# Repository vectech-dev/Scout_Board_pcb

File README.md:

# Pinout for Scout Board

## Motor Control

* In1 - GPIO_21/J3_18
* In2 - GPIO_35/J3_13

## Motor Switches

* Sw1 - GPIO_15/J1_8
* Sw2 - GPIO_6/J1_6

## Buttons 

* Flip Button - GPIO_7/J1_7
* Capture Button - GPIO_18/J1_11

## SBC

* Power - GPIO_8/J1_12

## Lights

* TopLights - Gpio_13/J1_19
* BottomLights - Gpio_14/J1_20

## Communication 

* RxD(ESP) - Gpio_16/J1_9
* TxD(ESP) - Gpio_17/J1_10

## Extra Provosions

* Button3 - Gpio_9
* Button4 - Gpio_10
* Button5 - Gpio_11
* Button6 - Gpio_12

* Conn1 - Gpio_2
* Conn2 - Gpio_3
* Conn3 - Gpio_4
* Conn4 - Gpio_5

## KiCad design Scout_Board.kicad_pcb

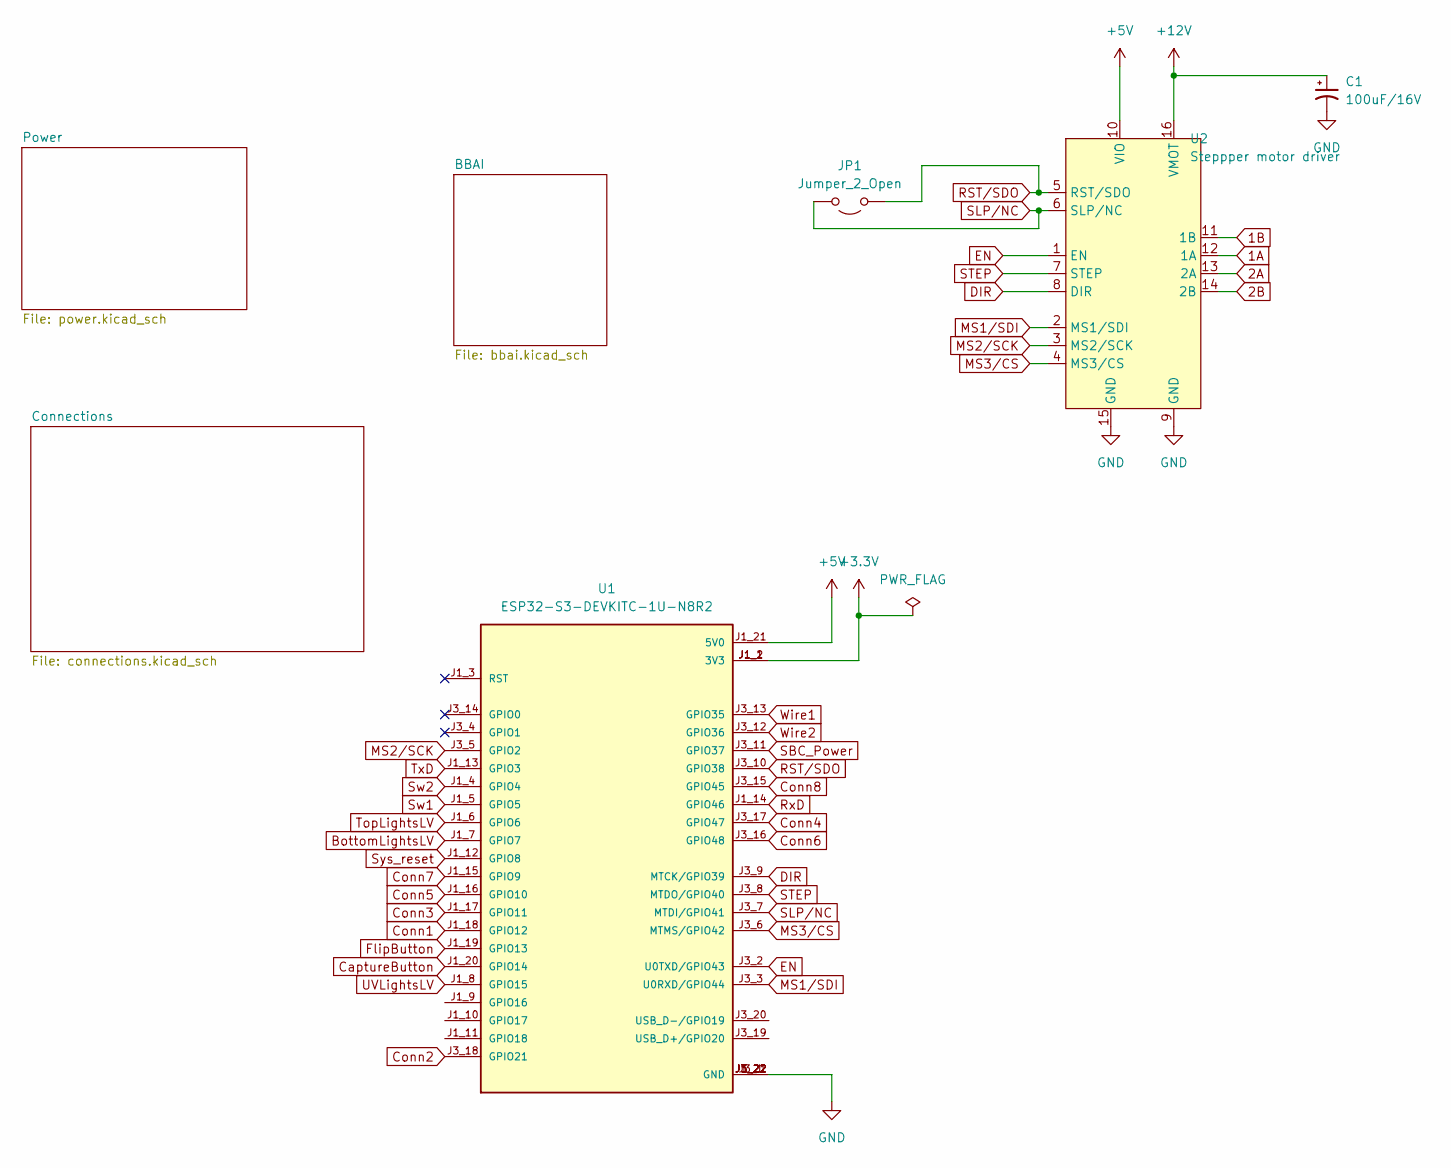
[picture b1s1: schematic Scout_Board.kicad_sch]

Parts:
C1: 100uF/16V; CP_Elec_6.3x5.9; Part Number 865080343009; LCSC C111600
JP1: Jumper_2_Open; TestPoint_2Pads_Pitch2.54mm_Drill0.8mm; LCSC C920781
U1: ESP32-S3-DEVKITC-1U-N8R2; XCVR_ESP32-S3-DEVKITC-1-N8R2; PARTREV 5.3
U2: Steppper motor driver; Pololu_Breakout-16_15.2x20.3mm

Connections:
1A: U2.12 (1A); also elsewhere on the board
1B: U2.11 (1B); also elsewhere on the board
2A: U2.13 (2A); also elsewhere on the board
2B: U2.14 (2B); also elsewhere on the board
5V: U1.J1_21 (5V0), U2.10 (VIO); also elsewhere on the board
+3.3V: U1.J1_1 (3V3), U1.J1_2 (3V3); also elsewhere on the board
+12V: C1.1, U2.16 (VMOT); also elsewhere on the board
BottomLightsLV: U1.J1_7 (GPIO7); also elsewhere on the board
CaptureButton: U1.J1_20 (GPIO14); also elsewhere on the board
Conn1: U1.J1_18 (GPIO12); also elsewhere on the board
Conn2: U1.J3_18 (GPIO21); also elsewhere on the board
Conn3: U1.J1_17 (GPIO11); also elsewhere on the board
Conn4: U1.J3_17 (GPIO47); also elsewhere on the board
Conn5: U1.J1_16 (GPIO10); also elsewhere on the board
Conn6: U1.J3_16 (GPIO48); also elsewhere on the board
Conn7: U1.J1_15 (GPIO9); also elsewhere on the board
Conn8: U1.J3_15 (GPIO45); also elsewhere on the board
DIR: U1.J3_9 (MTCK/GPIO39), U2.8 (DIR)
EN: U1.J3_2 (U0TXD/GPIO43), U2.1 (EN)
FlipButton: U1.J1_19 (GPIO13); also elsewhere on the board
GND: C1.2, U1.J1_22 (GND), U1.J3_1 (GND), U1.J3_21 (GND), U1.J3_22 (GND), U2.9 (GND), U2.15 (GND); also elsewhere on the board
MS1/SDI: U1.J3_3 (U0RXD/GPIO44), U2.2 (MS1/SDI)
MS2/SCK: U1.J3_5 (GPIO2), U2.3 (MS2/SCK)
MS3/CS: U1.J3_6 (MTMS/GPIO42), U2.4 (MS3/CS)
RST/SDO: JP1.1 (A), U1.J3_10 (GPIO38), U2.5 (RST/SDO)
RxD: U1.J1_14 (GPIO46); also elsewhere on the board
SBC_Power: U1.J3_11 (GPIO37); also elsewhere on the board
SLP/NC: JP1.2 (B), U1.J3_7 (MTDI/GPIO41), U2.6 (SLP/NC)
STEP: U1.J3_8 (MTDO/GPIO40), U2.7 (STEP)
Sw1: U1.J1_5 (GPIO5); also elsewhere on the board
Sw2: U1.J1_4 (GPIO4); also elsewhere on the board
Sys_reset: U1.J1_12 (GPIO8); also elsewhere on the board
TopLightsLV: U1.J1_6 (GPIO6); also elsewhere on the board
TxD: U1.J1_13 (GPIO3); also elsewhere on the board
UVLightsLV: U1.J1_8 (GPIO15); also elsewhere on the board
Wire1: U1.J3_13 (GPIO35); also elsewhere on the board
Wire2: U1.J3_12 (GPIO36); also elsewhere on the board

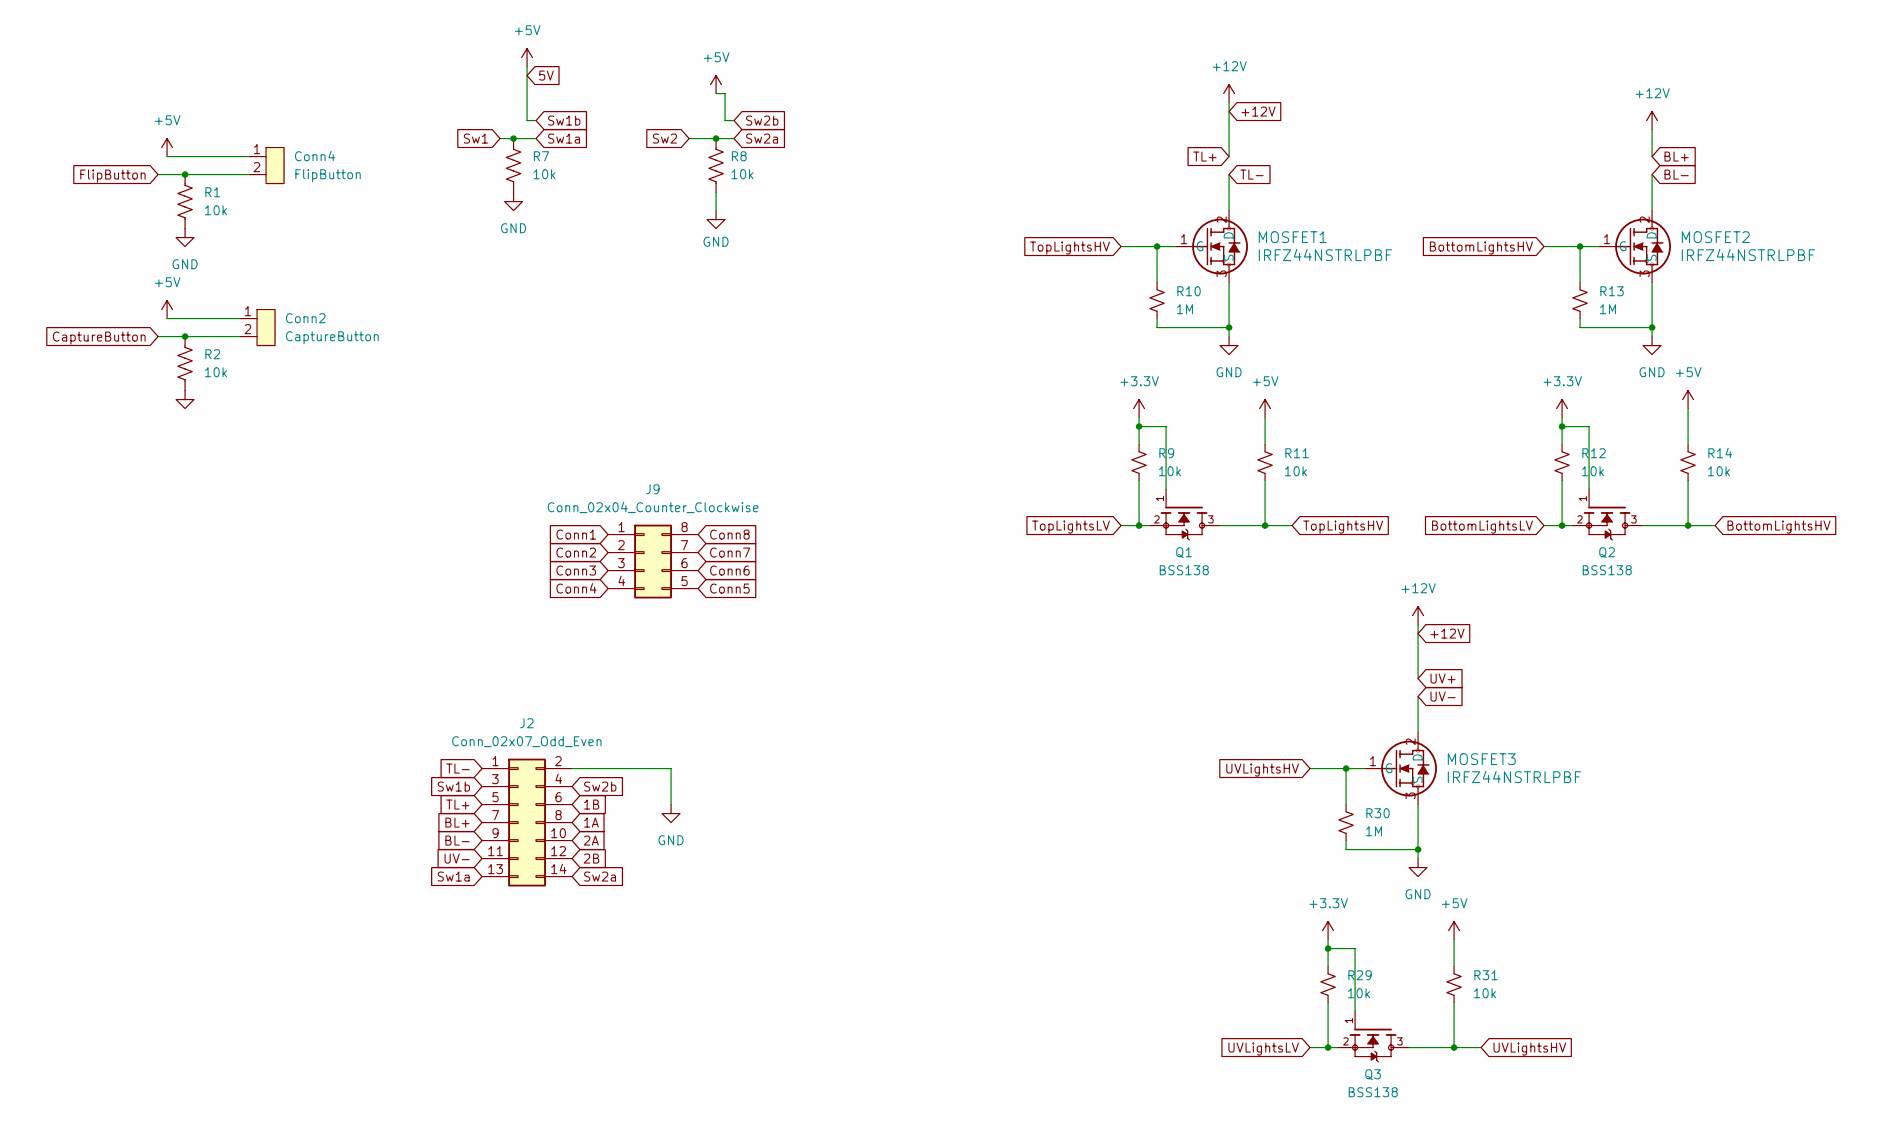
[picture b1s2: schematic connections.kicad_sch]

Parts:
Conn2: CaptureButton; JST_XH_B2B-XH-AM_1x02_P2.50mm_Vertical; Part Number B2B-XH-A-M; LCSC C158012
Conn4: FlipButton; JST_XH_B2B-XH-AM_1x02_P2.50mm_Vertical; Part Number B2B-XH-A-M; LCSC C158012
J2: Conn_02x07_Odd_Even; IDC-Header_2x07_P2.54mm_Vertical; Part Number 3020-14-0100-00; LCSC C17661375
J9: Conn_02x04_Counter_Clockwise; PinSocket_2x04_P2.54mm_Vertical
MOSFET1, MOSFET2, MOSFET3: IRFZ44NSTRLPBF; DPAK254P1524X483-3N; Part Number IRFZ44NSTRLPBF; LCSC C58228
Q1, Q2, Q3: BSS138; SOT-323_DIO; PARTREV 30 Jan 2018; LCSC C5250986
R1, R2, R7, R8, R9, R11, R12, R14, R29, R31: 10k; R_0603_1608Metric_Pad0.98x0.95mm_HandSolder; Part Number RMCF0603JT10K0; LCSC C98220
R10, R13, R30: 1M; R_0603_1608Metric_Pad0.98x0.95mm_HandSolder; Part Number ERJ-3EKF1004V; LCSC C4060339

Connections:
1A: J2.8; also elsewhere on the board
1B: J2.6; also elsewhere on the board
2A: J2.10; also elsewhere on the board
2B: J2.12; also elsewhere on the board
5V: Conn2.1, Conn4.1, J2.3, J2.4, R11.1, R14.1, R31.1; also elsewhere on the board
+3.3V: Q1.1, Q2.1, Q3.1, R9.1, R12.1, R29.1; also elsewhere on the board
+12V: J2.5, J2.7; also elsewhere on the board
BL-: J2.9, MOSFET2.2 (D)
BottomLightsHV: MOSFET2.1 (G), Q2.3, R13.1, R14.2
BottomLightsLV: Q2.2, R12.2; also elsewhere on the board
CaptureButton: Conn2.2, R2.1; also elsewhere on the board
Conn1: J9.1; also elsewhere on the board
Conn2: J9.2; also elsewhere on the board
Conn3: J9.3; also elsewhere on the board
Conn4: J9.4; also elsewhere on the board
Conn5: J9.5; also elsewhere on the board
Conn6: J9.6; also elsewhere on the board
Conn7: J9.7; also elsewhere on the board
Conn8: J9.8; also elsewhere on the board
FlipButton: Conn4.2, R1.1; also elsewhere on the board
GND: J2.2, MOSFET1.3 (S), MOSFET2.3 (S), MOSFET3.3 (S), R1.2, R2.2, R7.2, R8.2, R10.2, R13.2, R30.2; also elsewhere on the board
Sw1: J2.13, R7.1; also elsewhere on the board
Sw2: J2.14, R8.1; also elsewhere on the board
TL-: J2.1, MOSFET1.2 (D)
TopLightsHV: MOSFET1.1 (G), Q1.3, R10.1, R11.2
TopLightsLV: Q1.2, R9.2; also elsewhere on the board
UV-: J2.11, MOSFET3.2 (D)
UVLightsHV: MOSFET3.1 (G), Q3.3, R30.1, R31.2
UVLightsLV: Q3.2, R29.2; also elsewhere on the board

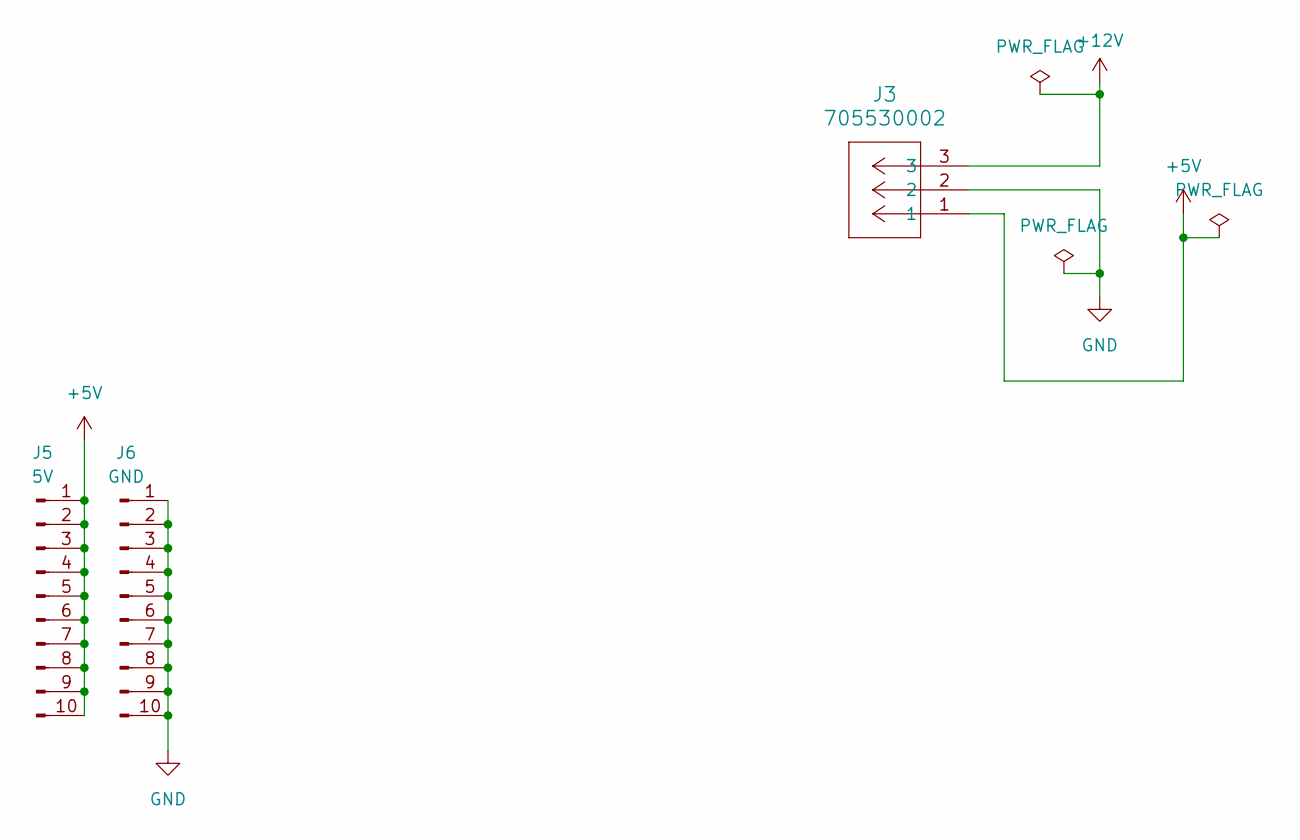
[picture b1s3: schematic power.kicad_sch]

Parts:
J3: 705530002; CONN3_53-0002_MOL; Part Number 705530002; LCSC C505296
J5: 5V; PinSocket_2x05_P2.54mm_Vertical
J6: GND; PinSocket_2x05_P2.54mm_Vertical

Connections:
5V: J3.1, J5.1, J5.2, J5.3, J5.4, J5.5, J5.6, J5.7, J5.8, J5.9, J5.10; also elsewhere on the board
+12V: J3.3; also elsewhere on the board
GND: J3.2, J6.1, J6.2, J6.3, J6.4, J6.5, J6.6, J6.7, J6.8, J6.9, J6.10; also elsewhere on the board

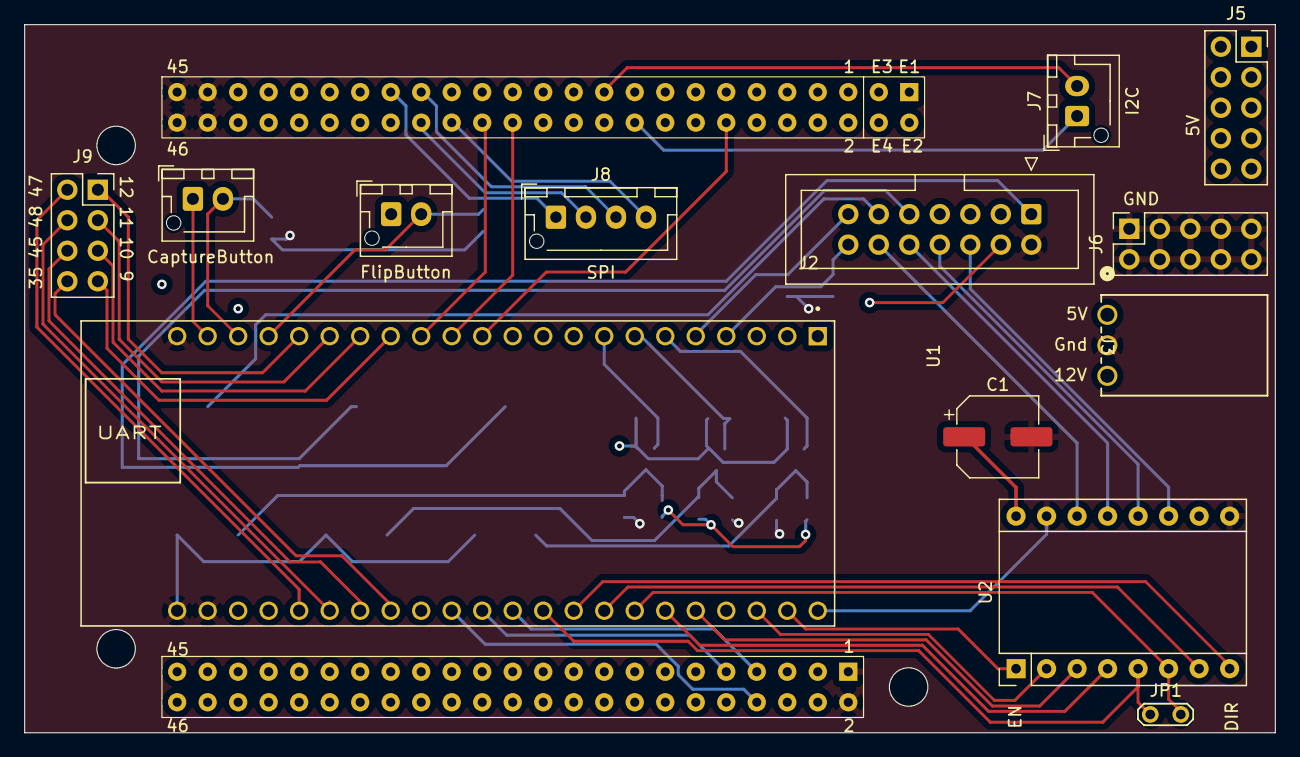
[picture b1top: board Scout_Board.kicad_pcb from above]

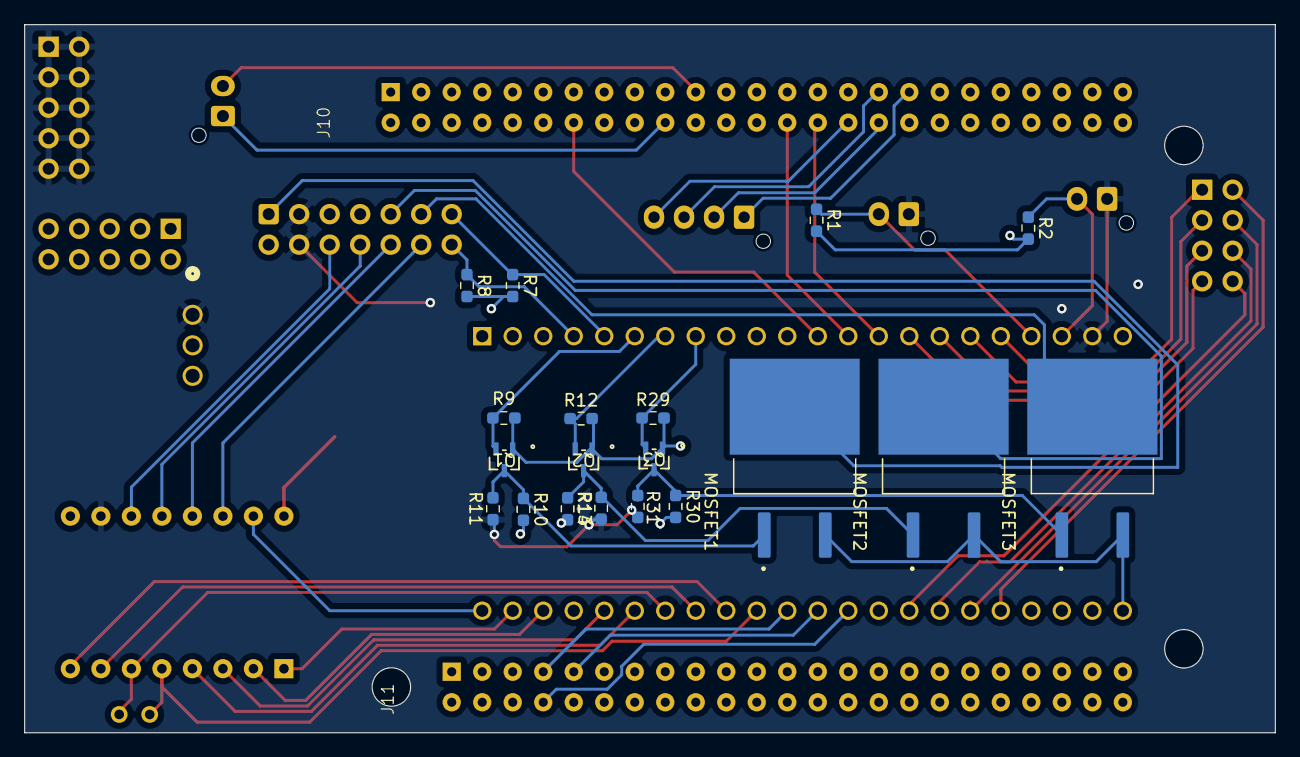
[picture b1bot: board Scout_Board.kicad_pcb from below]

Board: 4 copper layers, 104.1 x 59.0 mm, 34 parts (21 on the bottom side), 49 nets.

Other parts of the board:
J7: I2C; JST_XH_B2B-XH-AM_1x02_P2.50mm_Vertical
J8: SPI; JST_XH_B4B-XH-AM_1x04_P2.50mm_Vertical
J10: BBAI_P9; BBAI-P9
J11: BBAI_P8; BBAI-P8

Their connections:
GND: J10.43 (GND), J10.44 (GND), J10.45 (GND), J10.46 (GND), J11.1 (GND), J11.2 (GND); also elsewhere on the board
I2C1_SCL: J7.2, J10.17 (GPIO0_28)
I2C1_SDA: J7.1, J10.16 (GPIO0_94)
RxD: J10.26 (GPIO0_118); also elsewhere on the board
SBC_Power: J11.7 (GPIO0_15); also elsewhere on the board
SPI1_CS0: J8.4, J10.28 (GPIO1_11)
SPI1_D0: J8.3, J10.29 (GPIO1_14)
SPI1_D1: J8.2, J10.30 (GPIO1_13)
SPI1_SCLK: J8.1, J10.31 (GPIO1_12)
Sys_reset: J10.10 (Reset); also elsewhere on the board
TxD: J10.24 (GPIO0_119); also elsewhere on the board
Wire1: J11.8 (GPIO0_14); also elsewhere on the board
Wire2: J11.9 (GPIO0_17); also elsewhere on the board

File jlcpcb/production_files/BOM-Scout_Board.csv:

Comment,Designator,Footprint,LCSC
100uF/16V,C1,CP_Elec_6.3x5.9,C111600
CaptureButton,"Conn2,Conn4,J7",JST_XH_B2B-XH-AM_1x02_P2.50mm_Vertical,C158012
SPI,J8,JST_XH_B4B-XH-AM_1x04_P2.50mm_Vertical,C161871
Conn_02x07_Odd_Even,J2,IDC-Header_2x07_P2.54mm_Vertical,C17661375
1M,"R10,R13,R30",R_0603_1608Metric_Pad0.98x0.95mm_HandSolder,C4060339
705530002,J3,CONN3_53-0002_MOL,C505296
BSS138,"Q1,Q2,Q3",SOT-323_DIO,C5250986
IRFZ44NSTRLPBF,"MOSFET1,MOSFET2,MOSFET3",DPAK254P1524X483-3N,C58228
BBAI_P8,J11,BBAI-P8,C725895
BBAI_P9,J10,BBAI-P9,C7501604
Jumper_2_Open,JP1,TestPoint_2Pads_Pitch2.54mm_Drill0.8mm,C920781
10k,"R1,R11,R12,R14,R2,R29,R31,R7,R8,R9",R_0603_1608Metric_Pad0.98x0.95mm_HandSolder,C98220
Steppper motor driver,U2,Pololu_Breakout-16_15.2x20.3mm,
Conn_02x04_Counter_Clockwise,J9,PinSocket_2x04_P2.54mm_Vertical,
GND,J6,PinSocket_2x05_P2.54mm_Vertical,
5V,J5,PinSocket_2x05_P2.54mm_Vertical,
ESP32-S3-DEVKITC-1U-N8R2,U1,XCVR_ESP32-S3-DEVKITC-1-N8R2,

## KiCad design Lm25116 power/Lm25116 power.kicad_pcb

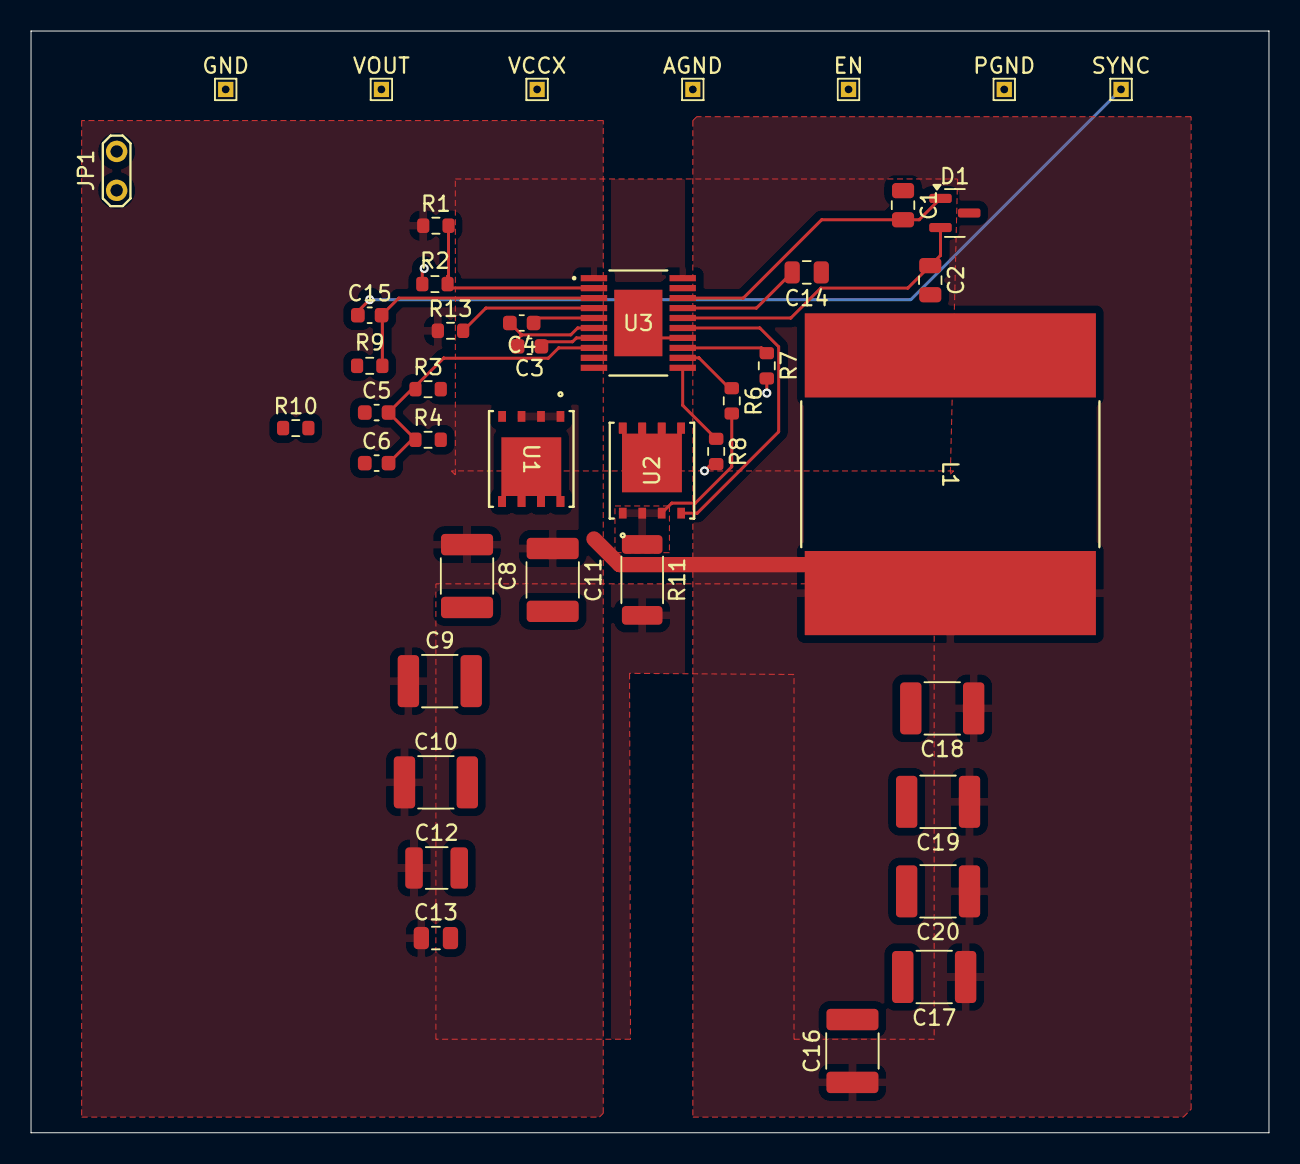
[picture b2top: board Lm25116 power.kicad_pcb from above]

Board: 2 copper layers, 80.8 x 71.9 mm, 43 parts (0 on the bottom side), 22 nets.

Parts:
C1, C2, C14: 1uF; C_0805_2012Metric
C3: 0.01uF; C_0603_1608Metric
C4: 270pF; C_0603_1608Metric
C5: 2.2uF; C_0603_1608Metric
C6: 3300pF; C_0603_1608Metric
C8, C9, C10, C11: 2.2uF; C_1812_4532Metric
C12: 1uF; C_1210_3225Metric
C13: 0.1uF; C_0805_2012Metric
C15: 100pF; C_0603_1608Metric
C16, C17, C18, C19, C20: 100uF; C_1812_4532Metric
D1: CMPD2003; SOT-23
JP1: Jumper_2_Small_Open; TestPoint_2Pads_Pitch2.54mm_Drill0.8mm
L1: 6uH; HC2LP
R1: 102k; R_0603_1608Metric
R2: 21k; R_0603_1608Metric
R3: 3.74k; R_0603_1608Metric
R4: 1.21k; R_0603_1608Metric
R6, R7: 0; R_0603_1608Metric
R8: 10k; R_0603_1608Metric
R9: 12.4k; R_0603_1608Metric
R10: 18k; R_0603_1608Metric
R11: 0.01; R_2010_5025Metric
R13: 1M; R_0603_1608Metric
TP1: SYNC; TestPoint_THTPad_1.0x1.0mm_Drill0.5mm
TP2: PGND; TestPoint_THTPad_1.0x1.0mm_Drill0.5mm
TP3: EN; TestPoint_THTPad_1.0x1.0mm_Drill0.5mm
TP4: AGND; TestPoint_THTPad_1.0x1.0mm_Drill0.5mm
TP5: VCCX; TestPoint_THTPad_1.0x1.0mm_Drill0.5mm
TP6: VOUT; TestPoint_THTPad_1.0x1.0mm_Drill0.5mm
TP7: GND; TestPoint_THTPad_1.0x1.0mm_Drill0.5mm
U1, U2: SI7850ADP-T1-GE3; MOSFET_7DP-T1-GE3_VIS
U3: LM25116MH; MXA20A_TEX-M

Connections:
+5V: C16.1, C17.1, C18.1, C19.1, C20.1, L1.2, R3.2, TP6.1, U3.10 (VOUT)
+12V: C8.1, C9.1, C10.1, C11.1, C12.1, C13.1, R1.1, R13.1, U1.5 (D), U1.6 (D), U1.7 (D), U1.8 (D), U3.1 (VIN)
GND: C2.2, C3.2, C4.2, C8.2, C9.2, C10.2, C11.2, C12.2, C13.2, C14.1, C16.2, C17.2, C18.2, C19.2, C20.2, JP1.1 (A), R2.2, R4.2, R7.2, R8.2, R9.2, R11.2, TP2.1, TP4.1, TP7.1, U3.6 (AGND), U3.14 (PGND), U3.21 (EP)
unnamed: C6.1, R10.2
unnamed: C15.1, TP1.1
unnamed: C2.1, D1.2 (A), U3.16 (VCC)
unnamed: C1.2, D1.1 (K), U3.18 (HB)
unnamed: R1.2, R2.1, U3.2 (ULVO)
unnamed: JP1.2 (B), R8.1, U3.11 (DEMB)
unnamed: R6.2, R11.1, U2.1 (S), U2.2 (S), U2.3 (S)
unnamed: U1.4 (G), U3.19 (HO)
unnamed: U2.4 (G), U3.15 (LO)
unnamed: C5.1, R10.1, U3.9 (COMP)
unnamed: R6.1, U3.12 (CS)
unnamed: R7.1, U3.13 (CSG)
unnamed: R13.2, TP3.1, U3.4 (EN)
unnamed: C5.2, C6.2, R3.1, R4.1, U3.8 (FB)
unnamed: C4.1, U3.5 (RAMP)
unnamed: C15.2, R9.1, U3.3 (RT/SYNC)
unnamed: C3.1, U3.7 (SS)
unnamed: C1.1, L1.1, U1.1 (S), U1.2 (S), U1.3 (S), U2.5 (D), U2.6 (D), U2.7 (D), U2.8 (D), U3.20 (SW)
unnamed: C14.2, TP5.1, U3.17 (VCCX)

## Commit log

2024-05-22 I don't know
2024-05-22 Base changes
    Deleted the redundant files.
2024-05-22 In process of adding top and bottom lights
2024-05-22 Circuit done except motor
    Need to add smd buttons.
2024-05-23 Finished circuit
2024-05-23 Updated the footprints for all the components.
2024-05-23 bavkups
2024-05-23 PCB Layout done
    Routing yet to do.
2024-05-24 Pcb - no errors
2024-05-27 PCB ready
2024-05-27 test
2024-06-06 last
2024-06-06 new version
2024-07-26 New Branch - Alpha2.0
2024-07-26 Removed motor and added A4988
2024-08-28 Added BOM
2024-09-17 Added motor driver
2024-09-17 MID CHANGES
2024-09-23 power board changes
2024-09-30 New board test
2024-09-30 Layout changes
2024-10-08 Layout updated with mounting holes
2024-10-09 Merging it with main
2024-11-27 Updated board
2024-11-27 Revert "Merge branch 'Alpha2.0' of https://github.com/vectech-dev/Scout_Board_pcb into Alpha2.0"
    This reverts commit 689b546a551de6080081789b571e82f20ea5beb2, reversing
    changes made to ec41f22121289bd8ebaadb64f54e8bd874968431.
2024-12-19 updated graphic files
